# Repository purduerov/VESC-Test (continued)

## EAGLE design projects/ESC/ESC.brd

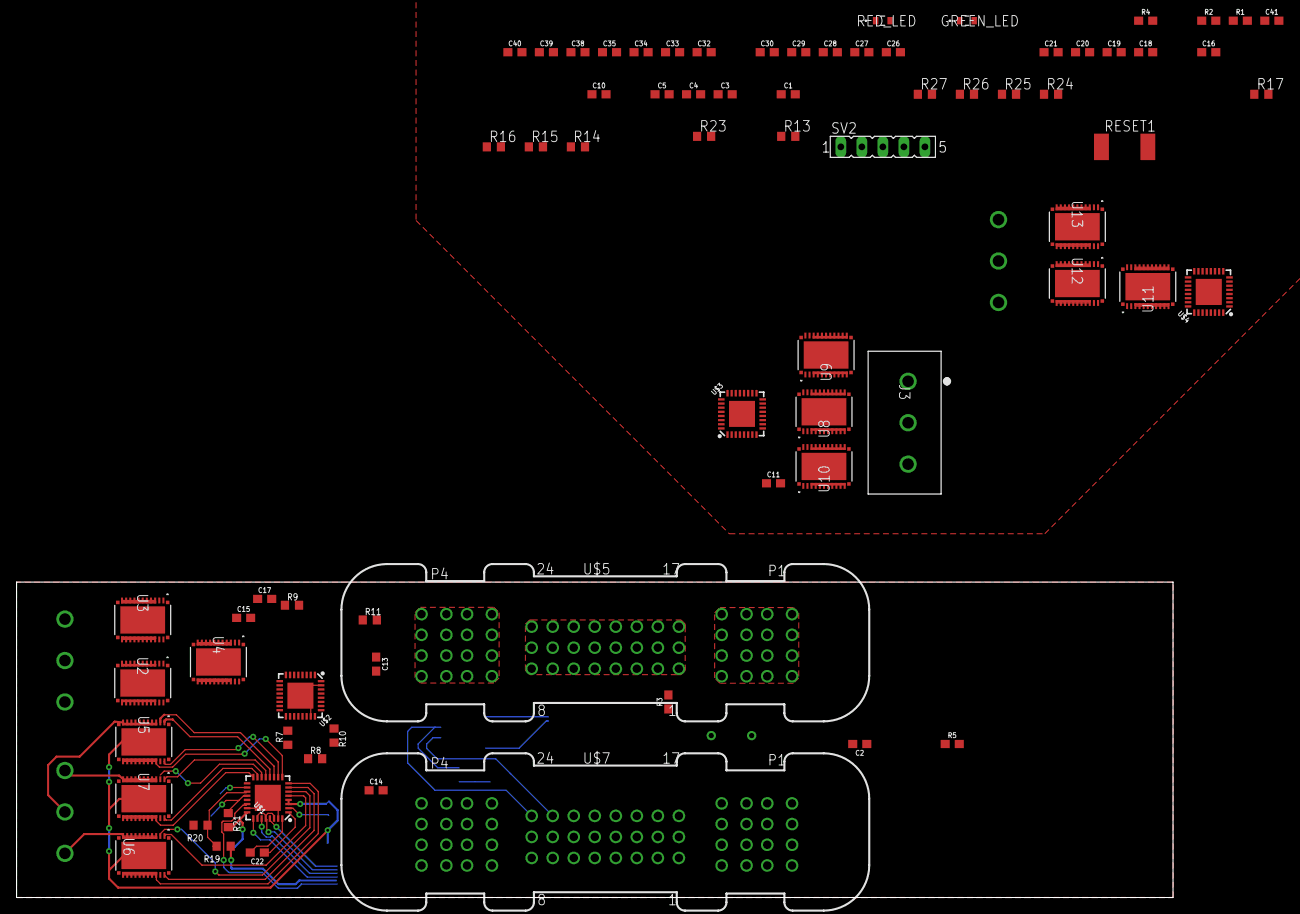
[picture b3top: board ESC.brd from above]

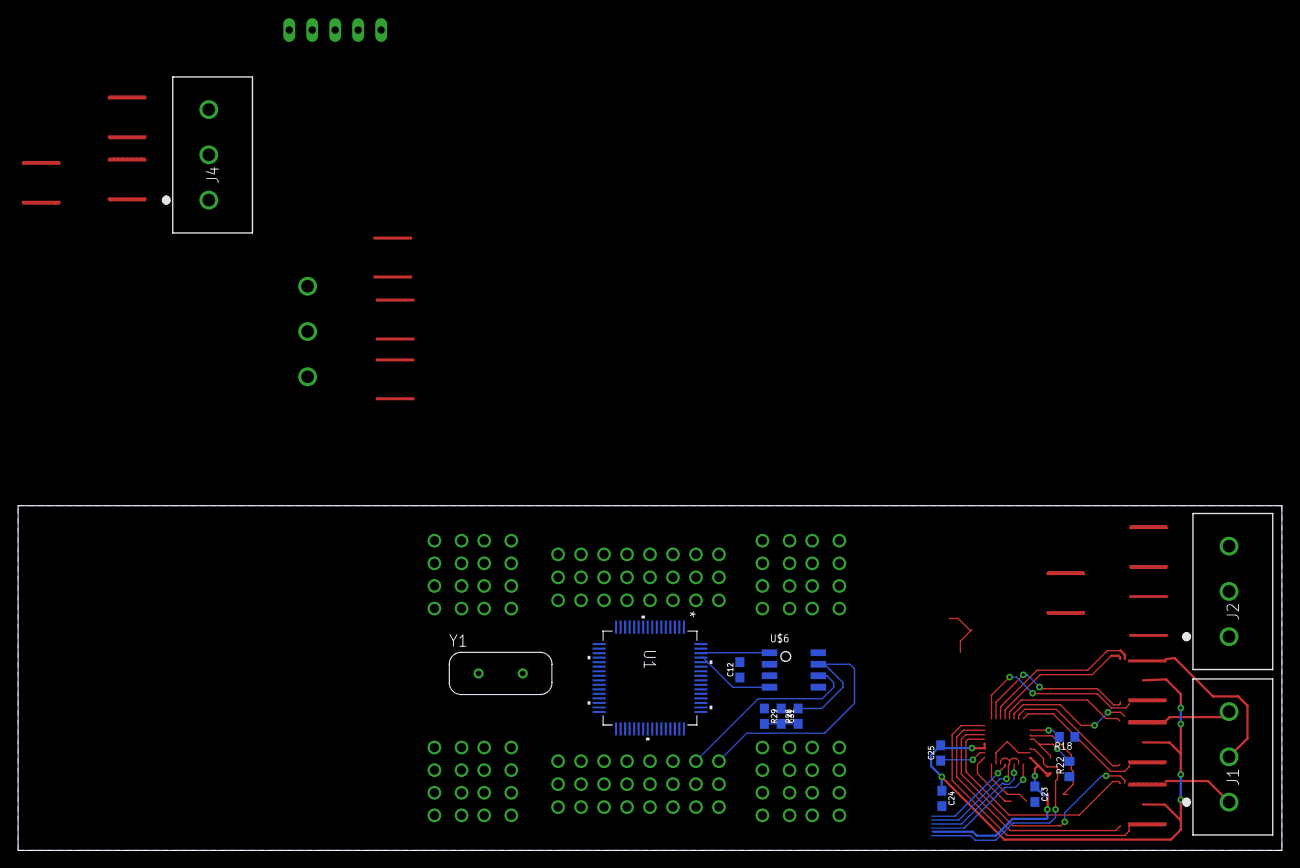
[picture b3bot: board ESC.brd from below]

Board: 2 copper layers, 139.7 x 38.1 mm, 91 parts (15 on the bottom side), 125 nets.

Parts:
C1, C3: 2.2uF; 0603
C2, C4, C5, C10, C11, C12, C16, C30, C32, C33, C34, C35, C38, C39, C40, C41: 4.7uF; 0603
C13, C18, C22, C26: 47nF; 0603
C14, C17, C19, C21, C23, C25, C27, C29: 1.0uF; 0603
C15, C20, C24, C28, C31: 0.1uF; 0603
GREEN_LED: TLMS1100-GS08; LED_VISHAY_TLMX1100
J1, J2, J3, J4: 1755529; CONN_1755529
R1, R2, R3, R4, R5: 1k; 0603
R7, R13, R18, R23: 47k; R0603
R8, R9, R10, R11, R14, R15, R16, R17, R19, R20, R21, R22, R24, R25, R26, R27: R0603
R28, R29: 60; 0603
RED_LED: TLMS1100-GS08; LED_VISHAY_TLMX1100
RESET1: SW_2512
SV2: FE05-1
U1: STM32F405RGT6; LQFP-64
U2, U3, U4, U5, U6, U7, U8, U9, U10, U11, U12, U13: CSD88584Q5DCT; DMM0022A
U$1, U$2, U$3, U$4: DRV8320H; QFN-32-5X5MM
U$5, U$7: SAMTEC
U$6: TCAN337D
Y1: ECS-80-S-4X; XTAL_ECS-80-S-4X

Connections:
3V3: U1.1, U1.13, U1.19, U1.32, U1.48, U1.64, U$5.1, U$5.2, U$5.3, U$5.4, U$5.5, U$5.6, U$5.7, U$5.8, U$5.9, U$5.10, U$5.11, U$5.12, U$5.13, U$5.14, U$5.15, U$5.16, U$5.17, U$5.18, U$5.19, U$5.20, U$5.21, U$5.22, U$5.23, U$5.24
12V: U$5.P1-1, U$5.P1-2, U$5.P1-3, U$5.P1-4, U$5.P1-5, U$5.P1-6, U$5.P1-7, U$5.P1-8, U$5.P2-1, U$5.P2-2, U$5.P2-3, U$5.P2-4, U$5.P2-5, U$5.P2-6, U$5.P2-7, U$5.P2-8, U$5.P3-1, U$5.P3-2, U$5.P3-3, U$5.P3-4, U$5.P3-5, U$5.P3-6, U$5.P3-7, U$5.P3-8, U$5.P4-1, U$5.P4-2, U$5.P4-3, U$5.P4-4, U$5.P4-5, U$5.P4-6, U$5.P4-7, U$5.P4-8
+3V3: C4.1, C5.1, C12.1, C16.1, C30.1, C32.1, C33.1, C34.1, C35.1, C38.1, C39.1, C40.1, C41.1, R4.2, SV2.5, U$6.VCC
CAN_H: R28.2, U$6.CANH, U$7.24
CAN_L: R29.1, U$6.CANL, U$7.23
CAN_RX: U1.61, U$6.RXD
CAN_TX: U1.62, U$6.TXD
DVDD_1: C14.1, R8.2, R10.2, U$2.24
DVDD_2: C23.1, R19.2, R21.2, U$1.24
DVDD_3: C19.1, R14.2, R16.2, U$3.24
DVDD_4: C27.1, R24.2, R26.2, U$4.24
EN_1: U1.37, U$2.22
EN_2: U1.43, U$1.22
EN_3: U1.54, U$3.22
EN_4: U1.27, U$4.22
GHA_1: U3.1, U$2.5
GHA_2: U6.1, U$1.5
GHA_3: U9.1, U$3.5
GHA_4: U12.1, U$4.5
GHB_1: U4.1, U$2.12
GHB_2: U5.1, U$1.12
GHB_3: U8.1, U$3.12
GHB_4: U11.1, U$4.12
GHC_1: U2.1, U$2.13
GHC_2: U7.1, U$1.13
GHC_3: U10.1, U$3.13
GHC_4: U13.1, U$4.13
GLA_1: U3.22, U$2.7
GLA_2: U6.22, U$1.7
GLA_3: U9.22, U$3.7
GLA_4: U12.22, U$4.7
GLB_1: U4.22, U$2.10
GLB_2: U5.22, U$1.10
GLB_3: U8.22, U$3.10
GLB_4: U11.22, U$4.10
GLC_1: U2.22, U$2.15
GLC_2: U7.22, U$1.15
GLC_3: U10.22, U$3.15
GLC_4: U13.22, U$4.15
GND: C1.2, C2.2, C3.2, C4.2, C5.2, C10.2, C11.2, C12.2, C14.2, C15.2, C16.2, C19.2, C20.2, C23.2, C24.2, C27.2, C28.2, C30.2, C31.1, C32.2, C33.2, C34.2, C35.2, C38.2, C39.2, C40.2, C41.2, GREEN_LED.1, R7.1, R9.1, R11.1, R13.1, R15.1, R17.1, R18.1, R20.1, R22.1, R23.1, R25.1, R27.1, RED_LED.1, RESET1.1, SV2.3, U1.12, U1.18, U1.60, U1.63, U$1.23, U$1.31, U$1.EP, U$2.23, U$2.31, U$2.EP, U$3.23, U$3.31, U$3.EP, U$4.23, U$4.31, U$4.EP, U$6.GND, U$7.P1-1, U$7.P1-2, U$7.P1-3, U$7.P1-4, U$7.P1-5, U$7.P1-6, U$7.P1-7, U$7.P1-8, U$7.P2-1, U$7.P2-2, U$7.P2-3, U$7.P2-4, U$7.P2-5, U$7.P2-6, U$7.P2-7, U$7.P2-8, U$7.P3-1, U$7.P3-2, U$7.P3-3, U$7.P3-4, U$7.P3-5, U$7.P3-6, U$7.P3-7, U$7.P3-8, U$7.P4-1, U$7.P4-2, U$7.P4-3, U$7.P4-4, U$7.P4-5, U$7.P4-6, U$7.P4-7, U$7.P4-8
IDRIVE: R19.1, R20.2, U$1.19
INHA_2: U1.42, U$1.25
INHB_2: U1.41, U$1.27
INHC_3: U1.51, U$1.29
INL_1: U1.33, U$2.26, U$2.28, U$2.30
INL_2: U1.39, U$1.26, U$1.28, U$1.30
INL_3: U1.50, U$3.26, U$3.28, U$3.30
INL_4: U1.56, U$4.26, U$4.28, U$4.30
unnamed: R1.2, U1.24
unnamed: GREEN_LED.2, R1.1
unnamed: R2.1, RED_LED.2
unnamed: R2.2, U1.25
unnamed: C1.1, U1.47
unnamed: C3.1, U1.31
unnamed: C11.1, R3.1, Y1.2
unnamed: C2.1, R5.1, Y1.1
unnamed: C13.1, U$2.1
unnamed: C13.2, U$2.32
unnamed: R8.1, R9.2, U$2.19
unnamed: R7.2, U$2.18
unnamed: R10.1, R11.2, U$2.20
unnamed: C21.1, U$3.2
unnamed: C18.1, U$3.1
unnamed: C18.2, U$3.32
unnamed: R14.1, R15.2, U$3.19
unnamed: R13.2, U$3.18
unnamed: R16.1, R17.2, U$3.20
unnamed: C25.1, U$1.2
unnamed: C22.1, U$1.1
unnamed: C22.2, U$1.32
unnamed: C17.1, U$2.2
unnamed: R18.2, U$1.18
unnamed: C29.1, U$4.2
unnamed: C26.1, U$4.1
unnamed: C26.2, U$4.32
unnamed: R24.1, R25.2, U$4.19
unnamed: R23.2, U$4.18
unnamed: R26.1, R27.2, U$4.20
unnamed: C31.2, R28.1, R29.2
NRST: C10.1, R4.1, RESET1.2, SV2.1, U1.7
OSC_IN: R5.2, U1.5
OSC_OUT: R3.2, U1.6
PHASE_A1: J2.1, U3.3, U3.4, U3.5, U3.6, U3.7, U3.8, U3.9, U3.10, U3.11
PHASE_A2: J1.1, U6.3, U6.4, U6.5, U6.6, U6.7, U6.8, U6.9, U6.10, U6.11
PHASE_A3: J3.1, U9.3, U9.4, U9.5, U9.6, U9.7, U9.8, U9.9, U9.10, U9.11
PHASE_A4: J4.1, U12.3, U12.4, U12.5, U12.6, U12.7, U12.8, U12.9, U12.10, U12.11
PHASE_B1: J2.2, U4.3, U4.4, U4.5, U4.6, U4.7, U4.8, U4.9, U4.10, U4.11
PHASE_B2: J1.2, U5.3, U5.4, U5.5, U5.6, U5.7, U5.8, U5.9, U5.10, U5.11
PHASE_B3: J3.2, U8.3, U8.4, U8.5, U8.6, U8.7, U8.8, U8.9, U8.10, U8.11
PHASE_B4: J4.2, U11.3, U11.4, U11.5, U11.6, U11.7, U11.8, U11.9, U11.10, U11.11
PHASE_C1: J2.3, U2.3, U2.4, U2.5, U2.6, U2.7, U2.8, U2.9, U2.10, U2.11
PHASE_C2: J1.3, U7.3, U7.4, U7.5, U7.6, U7.7, U7.8, U7.9, U7.10, U7.11
PHASE_C3: J3.3, U10.3, U10.4, U10.5, U10.6, U10.7, U10.8, U10.9, U10.10, U10.11
PHASE_C4: J4.3, U13.3, U13.4, U13.5, U13.6, U13.7, U13.8, U13.9, U13.10, U13.11
SHA_1: U3.2, U$2.6
SHA_2: U6.2, U$1.6
SHA_3: U9.2, U$3.6
SHA_4: U12.2, U$4.6
SHB_1: U4.2, U$2.11
SHB_2: U5.2, U$1.11
SHB_3: U8.2, U$3.11
SHB_4: U11.2, U$4.11
SHC_1: U2.2, U$2.14
SHC_2: U7.2, U$1.14
SHC_3: U10.2, U$3.14
SHC_4: U13.2, U$4.14
SLA_1: U3.12, U3.13, U3.14, U3.15, U3.16, U3.17, U3.18, U3.19, U3.20, U$2.8
SLA_2: U6.12, U6.13, U6.14, U6.15, U6.16, U6.17, U6.18, U6.19, U6.20, U$1.8
SLA_3: U9.12, U9.13, U9.14, U9.15, U9.16, U9.17, U9.18, U9.19, U9.20, U$3.8
SLA_4: U12.12, U12.13, U12.14, U12.15, U12.16, U12.17, U12.18, U12.19, U12.20, U$4.8
SLB_2: U5.12, U5.13, U5.14, U5.15, U5.16, U5.17, U5.18, U5.19, U5.20, U$1.9
SLB_3: U8.12, U8.13, U8.14, U8.15, U8.16, U8.17, U8.18, U8.19, U8.20, U$3.9
SLB_4: U11.12, U11.13, U11.14, U11.15, U11.16, U11.17, U11.18, U11.19, U11.20, U$4.9
SLC_1: U2.12, U2.13, U2.14, U2.15, U2.16, U2.17, U2.18, U2.19, U2.20, U$2.16
SLC_1B: U4.12, U4.13, U4.14, U4.15, U4.16, U4.17, U4.18, U4.19, U4.20
SLC_2: U7.12, U7.13, U7.14, U7.15, U7.16, U7.17, U7.18, U7.19, U7.20, U$1.16
SLC_3: U10.12, U10.13, U10.14, U10.15, U10.16, U10.17, U10.18, U10.19, U10.20, U$3.16
SLC_4: U13.12, U13.13, U13.14, U13.15, U13.16, U13.17, U13.18, U13.19, U13.20, U$4.16
SWCLK: SV2.4, U1.49
SWDIO: SV2.2, U1.46
VDS: R21.1, R22.2, U$1.20
VM_1: C15.1, C17.2, U2.27, U3.27, U4.27, U$2.3, U$2.4
VM_2: C24.1, C25.2, U5.27, U6.27, U7.27, U$1.3, U$1.4
VM_3: C20.1, C21.2, U8.27, U9.27, U10.27, U$3.3, U$3.4
VM_4: C28.1, C29.2, U11.27, U12.27, U13.27, U$4.3, U$4.4

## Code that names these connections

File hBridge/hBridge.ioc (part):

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Mcu.Name=STM32F405RGTx
Mcu.Package=LQFP64
Mcu.UserName=STM32F405RGTx
PA2.Signal=S_TIM2_CH3
PA5.Signal=S_TIM2_CH1_ETR
PB12.GPIOParameters=GPIO_Label
PB12.GPIO_Label=IN_L_A
PB12.Signal=GPIO_Output
PB13.GPIOParameters=GPIO_Label
PB13.GPIO_Label=IN_H3_A
PB13.Signal=GPIO_Output
PB14.GPIOParameters=GPIO_Label
PB14.GPIO_Label=IN_H2_A
PB14.Signal=GPIO_Output
PB15.GPIOParameters=GPIO_Label
PB15.GPIO_Label=IN_H1_A
PB15.Signal=GPIO_Output
PB3.Signal=S_TIM2_CH2
PC4.GPIOParameters=GPIO_Label
PC4.GPIO_Label=Green LED
PC4.Signal=GPIO_Output
PC5.GPIOParameters=GPIO_Label
PC5.GPIO_Label=Red LED
PC5.Signal=GPIO_Output
PC6.GPIOParameters=GPIO_Label
PC6.GPIO_Label=EN_A
PC6.Signal=GPIO_Output
RCC.HSE_VALUE=25000000
RCC.SYSCLKFreq_VALUE=16000000
board=custom

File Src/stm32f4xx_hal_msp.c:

/**
  ******************************************************************************
  * File Name          : stm32f4xx_hal_msp.c
  * Description        : This file provides code for the MSP Initialization 
  *                      and de-Initialization codes.
  ******************************************************************************
  ** This notice applies to any and all portions of this file
  * that are not between comment pairs USER CODE BEGIN and
  * USER CODE END. Other portions of this file, whether 
  * inserted by the user or by software development tools
  * are owned by their respective copyright owners.
  *
  * COPYRIGHT(c) 2018 STMicroelectronics
  *
  * Redistribution and use in source and binary forms, with or without modification,
  * are permitted provided that the following conditions are met:
  *   1. Redistributions of source code must retain the above copyright notice,
  *      this list of conditions and the following disclaimer.
  *   2. Redistributions in binary form must reproduce the above copyright notice,
  *      this list of conditions and the following disclaimer in the documentation
  *      and/or other materials provided with the distribution.
  *   3. Neither the name of STMicroelectronics nor the names of its contributors
  *      may be used to endorse or promote products derived from this software
  *      without specific prior written permission.
  *
  * THIS SOFTWARE IS PROVIDED BY THE COPYRIGHT HOLDERS AND CONTRIBUTORS "AS IS"
  * AND ANY EXPRESS OR IMPLIED WARRANTIES, INCLUDING, BUT NOT LIMITED TO, THE
  * IMPLIED WARRANTIES OF MERCHANTABILITY AND FITNESS FOR A PARTICULAR PURPOSE ARE
  * DISCLAIMED. IN NO EVENT SHALL THE COPYRIGHT HOLDER OR CONTRIBUTORS BE LIABLE
  * FOR ANY DIRECT, INDIRECT, INCIDENTAL, SPECIAL, EXEMPLARY, OR CONSEQUENTIAL
  * DAMAGES (INCLUDING, BUT NOT LIMITED TO, PROCUREMENT OF SUBSTITUTE GOODS OR
  * SERVICES; LOSS OF USE, DATA, OR PROFITS; OR BUSINESS INTERRUPTION) HOWEVER
  * CAUSED AND ON ANY THEORY OF LIABILITY, WHETHER IN CONTRACT, STRICT LIABILITY,
  * OR TORT (INCLUDING NEGLIGENCE OR OTHERWISE) ARISING IN ANY WAY OUT OF THE USE
  * OF THIS SOFTWARE, EVEN IF ADVISED OF THE POSSIBILITY OF SUCH DAMAGE.
  *
  ******************************************************************************
  */
/* Includes ------------------------------------------------------------------*/
#include "stm32f4xx_hal.h"
extern void _Error_Handler(char *, int);
/* USER CODE BEGIN 0 */

/* USER CODE END 0 */
                        
void HAL_TIM_MspPostInit(TIM_HandleTypeDef *htim);
                    /**
  * Initializes the Global MSP.
  */
void HAL_MspInit(void)
{
  /* USER CODE BEGIN MspInit 0 */

  /* USER CODE END MspInit 0 */

  __HAL_RCC_SYSCFG_CLK_ENABLE();
  __HAL_RCC_PWR_CLK_ENABLE();

  HAL_NVIC_SetPriorityGrouping(NVIC_PRIORITYGROUP_0);

  /* System interrupt init*/
  /* MemoryManagement_IRQn interrupt configuration */
  HAL_NVIC_SetPriority(MemoryManagement_IRQn, 0, 0);
  /* BusFault_IRQn interrupt configuration */
  HAL_NVIC_SetPriority(BusFault_IRQn, 0, 0);
  /* UsageFault_IRQn interrupt configuration */
  HAL_NVIC_SetPriority(UsageFault_IRQn, 0, 0);
  /* SVCall_IRQn interrupt configuration */
  HAL_NVIC_SetPriority(SVCall_IRQn, 0, 0);
  /* DebugMonitor_IRQn interrupt configuration */
  HAL_NVIC_SetPriority(DebugMonitor_IRQn, 0, 0);
  /* PendSV_IRQn interrupt configuration */
  HAL_NVIC_SetPriority(PendSV_IRQn, 0, 0);
  /* SysTick_IRQn interrupt configuration */
  HAL_NVIC_SetPriority(SysTick_IRQn, 0, 0);

  /* USER CODE BEGIN MspInit 1 */

  /* USER CODE END MspInit 1 */
}

void HAL_TIM_Base_MspInit(TIM_HandleTypeDef* htim_base)
{

  if(htim_base->Instance==TIM2)
  {
  /* USER CODE BEGIN TIM2_MspInit 0 */

  /* USER CODE END TIM2_MspInit 0 */
    /* Peripheral clock enable */
    __HAL_RCC_TIM2_CLK_ENABLE();
    /* TIM2 interrupt Init */
    HAL_NVIC_SetPriority(TIM2_IRQn, 0, 0);
    HAL_NVIC_EnableIRQ(TIM2_IRQn);
  /* USER CODE BEGIN TIM2_MspInit 1 */

  /* USER CODE END TIM2_MspInit 1 */
  }

}

void HAL_TIM_MspPostInit(TIM_HandleTypeDef* htim)
{

  GPIO_InitTypeDef GPIO_InitStruct;
  if(htim->Instance==TIM2)
  {
  /* USER CODE BEGIN TIM2_MspPostInit 0 */

  /* USER CODE END TIM2_MspPostInit 0 */
  
    /**TIM2 GPIO Configuration    
    PA0-WKUP     ------> TIM2_CH1
    PA1     ------> TIM2_CH2
    PB10     ------> TIM2_CH3 
    */
    GPIO_InitStruct.Pin = GPIO_PIN_0|GPIO_PIN_1;
    GPIO_InitStruct.Mode = GPIO_MODE_AF_PP;
    GPIO_InitStruct.Pull = GPIO_NOPULL;
    GPIO_InitStruct.Speed = GPIO_SPEED_FREQ_LOW;
    GPIO_InitStruct.Alternate = GPIO_AF1_TIM2;
    HAL_GPIO_Init(GPIOA, &GPIO_InitStruct);

    GPIO_InitStruct.Pin = GPIO_PIN_10;
    GPIO_InitStruct.Mode = GPIO_MODE_AF_PP;
    GPIO_InitStruct.Pull = GPIO_NOPULL;
    GPIO_InitStruct.Speed = GPIO_SPEED_FREQ_LOW;
    GPIO_InitStruct.Alternate = GPIO_AF1_TIM2;
    HAL_GPIO_Init(GPIOB, &GPIO_InitStruct);

  /* USER CODE BEGIN TIM2_MspPostInit 1 */

  /* USER CODE END TIM2_MspPostInit 1 */
  }

}

void HAL_TIM_Base_MspDeInit(TIM_HandleTypeDef* htim_base)
{

  if(htim_base->Instance==TIM2)
  {
  /* USER CODE BEGIN TIM2_MspDeInit 0 */

  /* USER CODE END TIM2_MspDeInit 0 */
    /* Peripheral clock disable */
    __HAL_RCC_TIM2_CLK_DISABLE();

    /* TIM2 interrupt DeInit */
    HAL_NVIC_DisableIRQ(TIM2_IRQn);
  /* USER CODE BEGIN TIM2_MspDeInit 1 */

  /* USER CODE END TIM2_MspDeInit 1 */
  }

}

void HAL_UART_MspInit(UART_HandleTypeDef* huart)
{

  GPIO_InitTypeDef GPIO_InitStruct;
  if(huart->Instance==USART2)
  {
  /* USER CODE BEGIN USART2_MspInit 0 */

  /* USER CODE END USART2_MspInit 0 */
    /* Peripheral clock enable */
    __HAL_RCC_USART2_CLK_ENABLE();
  
    /**USART2 GPIO Configuration    
    PA2     ------> USART2_TX
    PA3     ------> USART2_RX 
    */
    GPIO_InitStruct.Pin = USART_TX_Pin|USART_RX_Pin;
    GPIO_InitStruct.Mode = GPIO_MODE_AF_PP;
    GPIO_InitStruct.Pull = GPIO_PULLUP;
    GPIO_InitStruct.Speed = GPIO_SPEED_FREQ_VERY_HIGH;
    GPIO_InitStruct.Alternate = GPIO_AF7_USART2;
    HAL_GPIO_Init(GPIOA, &GPIO_InitStruct);

  /* USER CODE BEGIN USART2_MspInit 1 */

  /* USER CODE END USART2_MspInit 1 */
  }

}

void HAL_UART_MspDeInit(UART_HandleTypeDef* huart)
{

  if(huart->Instance==USART2)
  {
  /* USER CODE BEGIN USART2_MspDeInit 0 */

  /* USER CODE END USART2_MspDeInit 0 */
    /* Peripheral clock disable */
    __HAL_RCC_USART2_CLK_DISABLE();
  
    /**USART2 GPIO Configuration    
    PA2     ------> USART2_TX
    PA3     ------> USART2_RX 
    */
    HAL_GPIO_DeInit(GPIOA, USART_TX_Pin|USART_RX_Pin);

  /* USER CODE BEGIN USART2_MspDeInit 1 */

  /* USER CODE END USART2_MspDeInit 1 */
  }

}

/* USER CODE BEGIN 1 */

/* USER CODE END 1 */

/**
  * @}
  */

/**
  * @}
  */

/************************ (C) COPYRIGHT STMicroelectronics *****END OF FILE****/

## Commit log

2018-10-13 Version 1.0 of the oscillating sine wave made by manipulating the PWM duty cycles. The offsets have been made to minimize the amount of logic, since math is faster than logic. The PWM channels are A0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
2018-11-01 Changed code to alternate the pins according to the cosine waves
2018-11-03 this is the code to run the sinusoidal wave on the nucleo, given that the custom may be broken
2018-11-08 This is the new working code in order to run the motor. It catches sometimes, but it was updated between testing and pushing this code.
2018-11-15 have the motor running up to speed with ramp code quite well. Cannot determine a good way to start yet, working on reading values using ADC
2018-11-29 New code that might or might not be modified
2018-11-29 new stuffz
2018-11-30 The new nonsense that might work, it drives the MOSFETS using a lazy way of the inverse of the PWMs
2019-01-12 multiplied the array positions by a factor of two and now it works like a charm yay!
2019-02-09 running code for the custom ESC. If you use an oscilloscope you get a sweet signal now
2019-02-23 Neat code put into functions! YAY!
2019-09-14 added Sam's altium sketch
2019-10-26 finally putting the board onto Github :
2019-10-26 moving things because git
2019-10-26 added all the stuff for the current VESC
2019-11-16 pushing some stuff
2019-11-23 some later things to do
2020-02-18 Labels
2020-03-25 some changes i made a while back and forgot to push
2021-01-29 mass push lol
2021-01-30 Add git ignore and stop tracking those files
2021-01-30 Remove backup and autorouter files and ignore them
2021-01-30 couple improvements to the board and datasheets
2021-01-30 progress
2021-01-30 grounded drain of low side fets and other improvements
2021-01-30 Consolidate test boards to one place
2021-02-07 Replace micro and driver. Remove CAN.
2021-02-07 Add motor driver bottom pad and breakout can rx/tx pins
2021-02-07 Switch to drv8343
2021-02-21 Tidy up the code a little
2021-03-04 updated board
2021-03-06 updated test board
2021-03-06 Use no thermal banana con part. Remove DS Store
2021-03-13 fixed errors
2021-03-14 fixed airwires
2021-03-20 Remove DS Store files
2021-03-20 Final touches before ordering
2021-03-21 Final changes before ordering
2021-03-22 Add schematic print out
2021-03-23 V1 test board schematic printout
2021-04-03 why was it ever named hbridge
2021-04-13 Switch PWM lines to be optimized for 3x PWM
